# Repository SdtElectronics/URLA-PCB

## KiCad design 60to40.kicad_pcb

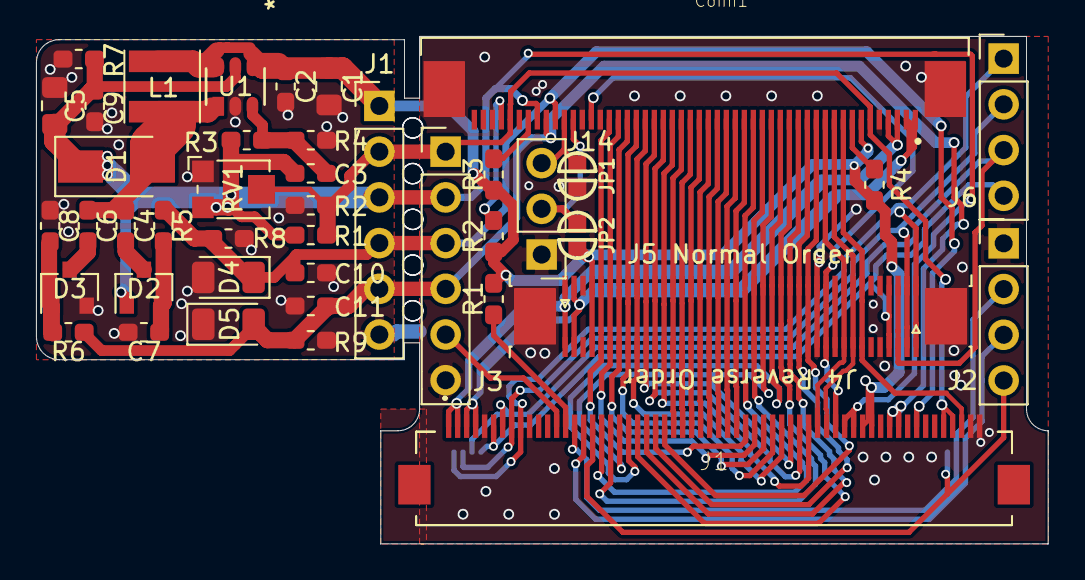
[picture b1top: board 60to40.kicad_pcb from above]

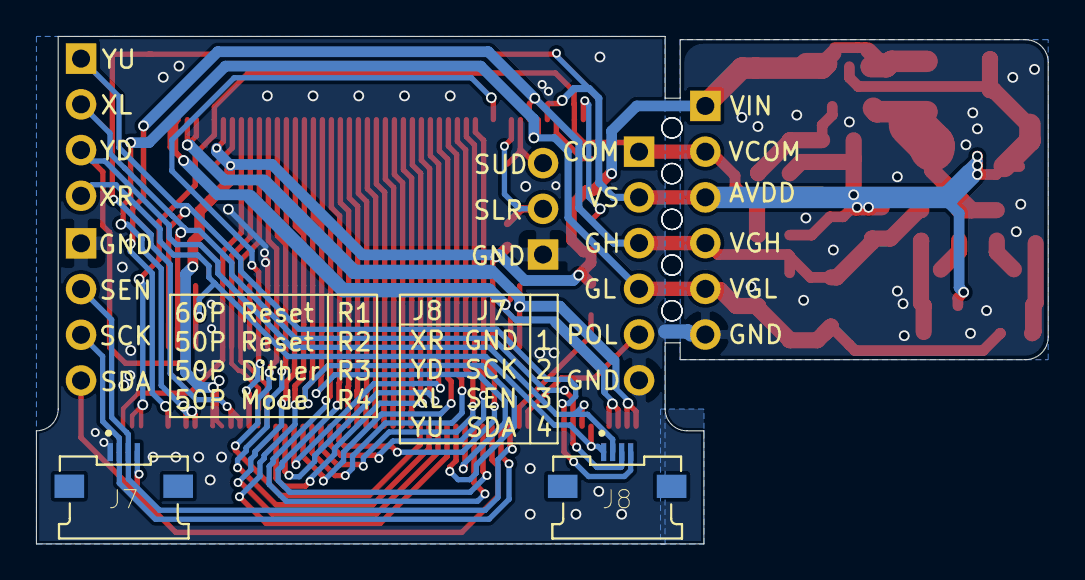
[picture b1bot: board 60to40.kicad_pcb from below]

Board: 2 copper layers, 56.2 x 28.2 mm, 45 parts (2 on the bottom side), 12 nets.

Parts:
C1: 10u; C_0805_2012Metric_Pad1.15x1.40mm_HandSolder
C2: 102; C_0603_1608Metric_Pad1.05x0.95mm_HandSolder
C3: NC; C_0603_1608Metric_Pad1.05x0.95mm_HandSolder
C4, C6, C7, C8, C9, C10, C11: 104; C_0603_1608Metric_Pad1.05x0.95mm_HandSolder
C5: 10uF; C_0805_2012Metric_Pad1.15x1.40mm_HandSolder
Conn1: FPC50pin; TE_5-1734592-0
D1: SS14; D_SMA
D2, D3: BAT54S; SOT-23
D4: 1N4744; D_1206_3216Metric
D5: 1N4736; D_1206_3216Metric
J1: 60P; XF3M60151B
J1#2, J3: Conn_01x06; PinHeader_1x06_P2.54mm_Vertical
J2, J6: Conn_01x04; PinHeader_1x04_P2.54mm_Vertical
J4 Reverse Order, J5 Normal Order: Conn_01x40; TE_4-1734839-0_1x40-1MP_P0.5mm_Horizontal
J7, J8: Conn_01x04; MOLEX_54548-0471
J14: Conn_01x03; PinHeader_1x03_P2.54mm_Vertical
JP1, JP2: Jumper; SOLDER-JUMPER_1-WAY
L1: 10uH; L_Taiyo-Yuden_MD-4040
R1, R1#2, R2, R2#2, R3, R4: R; R_0603_1608Metric_Pad1.05x0.95mm_HandSolder
R3#2: 51k; R_0603_1608Metric_Pad1.05x0.95mm_HandSolder
R4#2: 1k; R_0603_1608Metric_Pad1.05x0.95mm_HandSolder
R5, R6: 1.5k; R_0603_1608Metric_Pad1.05x0.95mm_HandSolder
R7: 20k; R_0603_1608Metric_Pad1.05x0.95mm_HandSolder
R8, R9: 47k; R_0603_1608Metric_Pad1.05x0.95mm_HandSolder
RV1: R_POT; Potentiometer_Bourns_TC33X_Vertical
U1: AP3019AKTR-G1

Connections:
/COM: J1#2.2, R1#2.1, R2#2.1, RV1.2
/GH: C10.1, D4.1, J1#2.4, R5.1, R8.1
/GL: C11.1, D5.2, J1#2.5, R6.1, R9.1
/VIN: C1.1, C2.1, J1#2.1, L1.1, U1.4, U1.6
/VS: C3.1, C5.1, C9.1, D1.1, D2.1, J1#2.3, R1#2.2, R3#2.1, R7.1, RV1.3, U1.5
GND: C1.2, C2.2, C5.2, C7.2, C8.2, C9.2, C10.2, C11.2, D3.2, D4.2, D5.1, J1#2.6, R2#2.2, R4#2.2, R7.2, R8.2, R9.2, RV1.1, U1.2
unnamed: C3.2, R3#2.2, R4#2.1, U1.3
unnamed: C4.1, D2.3
unnamed: C4.2, C6.2, D1.2, L1.2, U1.1
unnamed: C6.1, D3.3
unnamed: C7.1, D2.2, R5.2
unnamed: C8.1, D3.1, R6.2

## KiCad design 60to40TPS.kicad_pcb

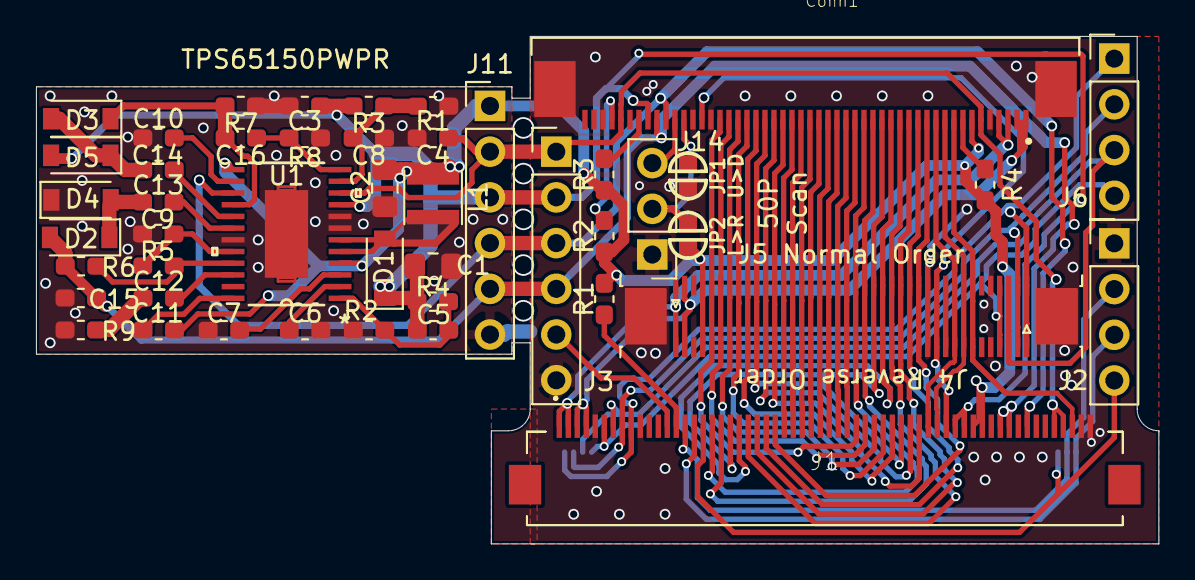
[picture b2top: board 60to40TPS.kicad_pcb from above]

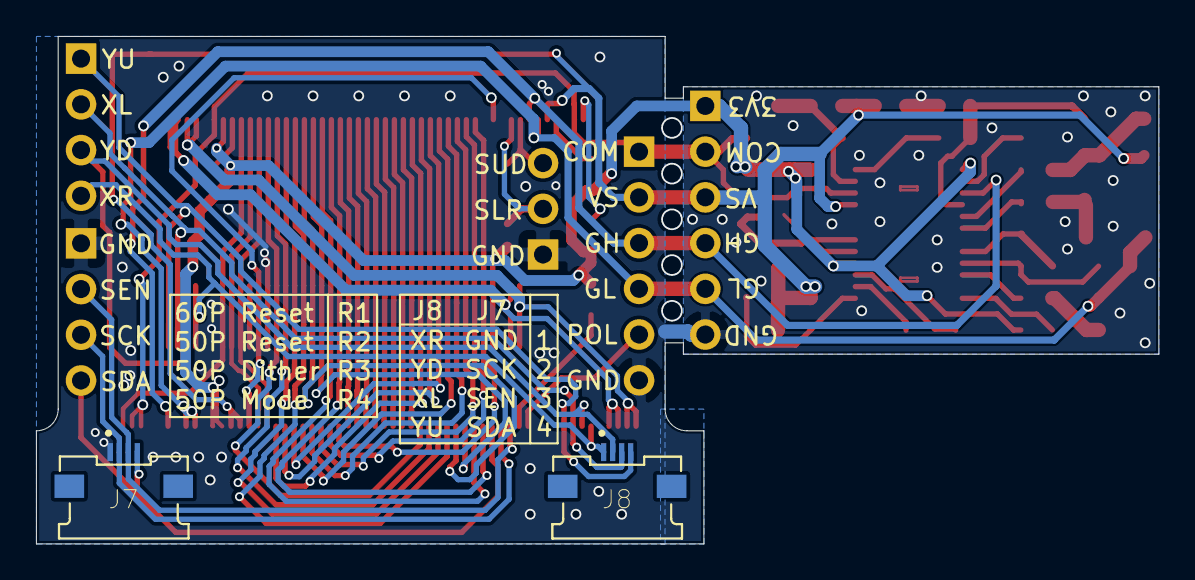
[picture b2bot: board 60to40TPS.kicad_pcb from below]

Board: 2 copper layers, 62.4 x 28.2 mm, 49 parts (2 on the bottom side), 51 nets.

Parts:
C1, C2: C; C_0805_2012Metric_Pad1.15x1.40mm_HandSolder
C3, C4, C5, C6, C7, C8, C9, C10, C11, C12, C13, C14, C15, C16: C; C_0603_1608Metric_Pad1.05x0.95mm_HandSolder
Conn1: FPC50pin; TE_5-1734592-0
D1, D2, D3, D4, D5: D_Schottky; D_SOD-123
J1: 60P; XF3M60151B
J2, J6: Conn_01x04; PinHeader_1x04_P2.54mm_Vertical
J3, J11: Conn_01x06; PinHeader_1x06_P2.54mm_Vertical
J4 Reverse Order, J5 Normal Order: Conn_01x40; TE_4-1734839-0_1x40-1MP_P0.5mm_Horizontal
J7, J8: Conn_01x04; MOLEX_54548-0471
J14: Conn_01x03; PinHeader_1x03_P2.54mm_Vertical
JP1, JP2: Jumper; SOLDER-JUMPER_1-WAY
L1: L; L_Taiyo-Yuden_NR-30xx
R1, R1#2, R2, R2#2, R3, R3#2, R4, R4#2, R5, R6, R7, R8, R9: R; R_0603_1608Metric_Pad1.05x0.95mm_HandSolder
U1: TPS65150PWPR

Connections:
+3V3: Conn1.7, J1.47, J1.48, J4 Reverse Order.37, J5 Normal Order.4, JP2.2, R1#2.1, R2#2.1, R3#2.1, R4#2.1
/B0: Conn1.19, J1.18, J4 Reverse Order.20, J5 Normal Order.21
/B1: Conn1.18, J1.19, J4 Reverse Order.19, J5 Normal Order.22
/B2: Conn1.17, J1.20, J4 Reverse Order.18, J5 Normal Order.23
/B3: Conn1.16, J1.21, J4 Reverse Order.17, J5 Normal Order.24
/B4: Conn1.15, J1.22, J4 Reverse Order.16, J5 Normal Order.25
/B5: Conn1.14, J1.23, J4 Reverse Order.15, J5 Normal Order.26
/B6: Conn1.13, J1.24, J4 Reverse Order.14, J5 Normal Order.27
/B7: Conn1.12, J1.25, J4 Reverse Order.13, J5 Normal Order.28
/GH: Conn1.41, J1.53, J3.3
/GL: Conn1.42, J1.50, J1.51, J3.4
/POL: J1.13, J3.5
/R0: Conn1.35, J1.34, J4 Reverse Order.36, J5 Normal Order.5
/R1: Conn1.34, J1.35, J4 Reverse Order.35, J5 Normal Order.6
/R2: Conn1.33, J1.36, J4 Reverse Order.34, J5 Normal Order.7
/R3: Conn1.32, J1.37, J4 Reverse Order.33, J5 Normal Order.8
/R4: Conn1.31, J1.38, J4 Reverse Order.32, J5 Normal Order.9
/R5: Conn1.30, J1.39, J4 Reverse Order.31, J5 Normal Order.10
/R6: Conn1.29, J1.40, J4 Reverse Order.30, J5 Normal Order.11
/R7: Conn1.28, J1.41, J4 Reverse Order.29, J5 Normal Order.12
/VS: Conn1.43, J1.45, J1.46, J3.2
/XL: J1.8, J4 Reverse Order.2, J5 Normal Order.39, J6.2, J8.3
/XR: J1.6, J4 Reverse Order.4, J5 Normal Order.37, J6.4, J8.1
/YD: J1.7, J4 Reverse Order.3, J5 Normal Order.38, J6.3, J8.2
/YU: J1.9, J4 Reverse Order.1, J5 Normal Order.40, J6.1, J8.4
/com: Conn1.6, Conn1.46, J1.56, J1.57, J3.1
GND: Conn1.5, Conn1.36, Conn1.38, Conn1.48, Conn1.S1, Conn1.S2, J1.5, J1.10, J1.59, J1.60, J2.1, J3.6, J4 Reverse Order.5, J4 Reverse Order.12, J4 Reverse Order.38, J4 Reverse Order.MP, J5 Normal Order.3, J5 Normal Order.29, J5 Normal Order.36, J5 Normal Order.MP, J7.1, J11.6, J14.1, JP1.2
unnamed: Conn1.1, Conn1.2, J1.3, J1.4, J4 Reverse Order.39, J5 Normal Order.2
unnamed: Conn1.3, Conn1.4, J1.1, J1.2, J4 Reverse Order.40, J5 Normal Order.1
unnamed: Conn1.8, R4#2.2
unnamed: Conn1.9, J1.58, J4 Reverse Order.7, J5 Normal Order.34
unnamed: Conn1.10, J1.43, J4 Reverse Order.8, J5 Normal Order.33
unnamed: Conn1.11, J1.42, J4 Reverse Order.9, J5 Normal Order.32
unnamed: Conn1.20, J1.33, J4 Reverse Order.21, J5 Normal Order.20
unnamed: Conn1.21, J1.32, J4 Reverse Order.22, J5 Normal Order.19
unnamed: Conn1.22, J1.31, J4 Reverse Order.23, J5 Normal Order.18
unnamed: Conn1.23, J1.30, J4 Reverse Order.24, J5 Normal Order.17
unnamed: Conn1.24, J1.29, J4 Reverse Order.25, J5 Normal Order.16
unnamed: Conn1.25, J1.28, J4 Reverse Order.26, J5 Normal Order.15
unnamed: Conn1.26, J1.27, J4 Reverse Order.27, J5 Normal Order.14
unnamed: Conn1.27, J1.26, J4 Reverse Order.28, J5 Normal Order.13
unnamed: Conn1.37, J1.44, J4 Reverse Order.11, J5 Normal Order.30
unnamed: Conn1.39, J14.2, JP2.1
unnamed: Conn1.40, J14.3, JP1.1
unnamed: Conn1.44, R3#2.2
unnamed: Conn1.47, R2#2.2
unnamed: J1.14, R1#2.2
unnamed: J1.15, J2.2, J7.3
unnamed: J1.16, J2.3, J7.2
unnamed: J1.17, J2.4, J7.4
unnamed: J4 Reverse Order.10, J5 Normal Order.31

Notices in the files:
parts and their libraries:
Copyright 2016 Accelerated Designs. All rights reserved.
